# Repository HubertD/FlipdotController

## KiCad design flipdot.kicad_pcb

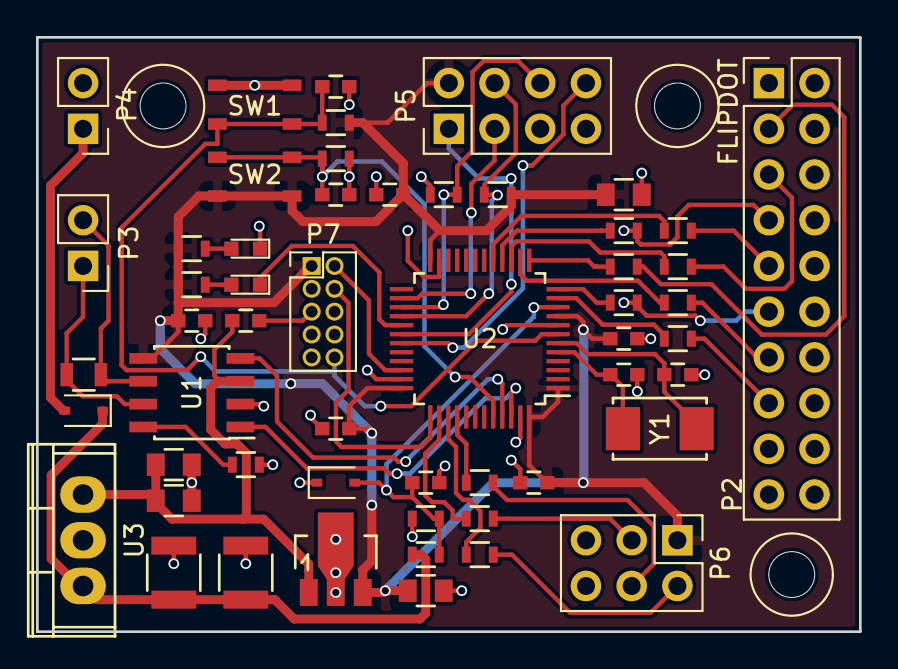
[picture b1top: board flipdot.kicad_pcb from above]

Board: 2 copper layers, 45.7 x 33.0 mm, 54 parts (0 on the bottom side), 45 nets.

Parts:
C1, C2: 20pF; C_0603
C3, C14, C16, C17: 10uF; C_0805
C4, C5, C6, C7, C8, C9, C10, C13, C15: 100nF; C_0603
C11, C12: 10uF; C_1210
D1: 3V9; SOD-323
D2: D_Schottky_Small; SOD-323
D4, D5: LED; LED_0603
P2: FLIPDOT; Pin_Header_Straight_2x10_Pitch2.54mm
P3: CAN; Pin_Header_Straight_1x02_Pitch2.54mm
P4: VCC; Pin_Header_Straight_1x02_Pitch2.54mm
P5: ESP8266-1; Pin_Header_Straight_2x04_Pitch2.54mm
P6: CONN_02X03; Pin_Header_Straight_2x03_Pitch2.54mm
P7: JTAG; Pin_Header_Straight_2x05_Pitch1.27mm
R1, R19: 1K; R_0603
R2: 120R; R_0805
R6, R7, R8, R9, R10, R11, R12, R16, R17, R18: 10R; R_0603
R13: 33K; R_0603
R14: 5K6; R_0603
R15, R23, R24: 10K; R_0603
R21, R22: R; R_0603
SW1, SW2: SW_Push; SKRPABE010
U1: TJA1051T/3; SOIC-8_3.9x4.9mm_Pitch1.27mm
U2: STM32F072C8Tx; LQFP-48_7x7mm_Pitch0.5mm
U3: LM7805CT; TO-220
U4: MCP1754ST-3302E/MB; SOT89-3_Housing
Y1: 8MHz; ABM3

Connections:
+3V3: C3.1, C4.1, C5.1, C6.1, C7.1, C8.1, C17.1, P5.2, P6.1, P7.1, R15.2, R21.1, R22.1, R23.2, SW2.2, U1.5, U2.1, U2.9, U2.24, U2.36, U2.48, U4.3
+5V: C9.1, C14.1, C16.1, U1.3, U3.3, U4.1
+24V: C11.1, C12.1, D2.1, R13.1, U3.1
BLACK_OE: R8.2, U2.16
BOOT: C15.1, R19.2, SW2.1, U2.44
CAN_H: P3.1, R2.1, U1.7
CAN_L: P3.2, R2.2, U1.6
CAN_RX: U1.4, U2.45
CAN_TX: U1.1, U2.46
COL_CLK: R10.2, U2.12
COL_DATA: R12.2, U2.11
ESP_GPIO0: P5.3, U2.26
ESP_NRST: P5.4, R23.1, U2.28
ESP_POWERON: P5.6, R24.2, U2.27
GND: C1.2, C2.2, C3.2, C4.2, C5.2, C6.2, C7.2, C8.2, C9.2, C10.2, C11.2, C12.2, C13.2, C14.2, C15.2, C16.2, C17.2, D1.1, D4.1, P2.4, P2.6, P2.8, P2.10, P2.12, P2.14, P2.16, P2.18, P2.20, P4.2, P5.7, P6.5, P6.6, P7.3, P7.5, R1.1, R14.1, R19.1, R24.1, SW1.1, U1.2, U2.8, U2.23, U2.35, U2.47, U3.2, U4.2
LED_USR: D5.1, U2.29
NES_CLK: R16.2, U2.39
NES_DATA: R18.2, U2.40
NES_LATCH: R17.2, U2.38
NRST: C13.1, P7.10, R15.1, SW1.2, U2.7
unnamed: C1.1, U2.5, Y1.1
unnamed: C2.1, U2.6, Y1.2
unnamed: D2.2, P4.1
unnamed: D4.2, R21.2
unnamed: D5.2, R22.2
unnamed: P2.3, R6.1
unnamed: P2.5, R7.1
unnamed: P2.7, R8.1
unnamed: P2.9, R9.1
unnamed: P2.11, R10.1
unnamed: P2.13, R11.1
unnamed: P2.15, R12.1
unnamed: P6.2, R16.1
unnamed: P6.3, R17.1
unnamed: P6.4, R18.1
unnamed: R1.2, U1.8
ROW_CLK: R11.2, U2.14
ROW_DATA: R6.2, U2.13
STROBE: R7.2, U2.15
SWCLK: P7.4, U2.37
SWDIO: P7.2, U2.34
UART_RX: P5.8, U2.31
UART_TX: P5.1, U2.30
VIN_ADC: C10.1, D1.2, R13.2, R14.2, U2.10
WHITE_OE: R9.2, U2.17

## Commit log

2017-01-08 add mounting holes
